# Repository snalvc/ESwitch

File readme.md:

# ESwitch

This is a high-side N-channel MOSFET electrical switch module. The power MOSFET (DMTH8003SPS) is driven by a high-side protection controller (LM5060). The schematics and PCB layout are designed in KiCad and available in the kicad directory. All the components are available in LCSC at least at the time of writing. It is also designed for single-sided PCBA with a few exceptions in the high current traces because you'll want them to be reinforced. Plus, I doubt XT90 can be assembled by cheap PCBAs anyway. There are also some Python utilities which are helpful for you to determine the required component values for various protections provided by the LM5060. In short:

- Calculate the required component values for the LM5060 with the help of programs in `utils`.
- Modify and generate the necessary manufacturing files in `kicad`.
- Have the PCB manufactured and assembled if you desire.
- Assemble the module with the instructions in `assemble`. You can also find the BOM there.

## TODO
- [ ] Fix XT90 socket and plug polarity
- [x] Add LCSC part numbers into schematics
- [ ] Add assemble instructions
- [ ] Add test results

## Debug Notes

I should have positioned the high-current traces on the bottom layer, allowing for reinforcement by adding solder or copper plates onto them.

Fortunately, by chance, I made a mistake with the XT90 socket and plug. Consequently, I can easily swap the socket and plug, relocating them to the back side of the board, thereby preventing any interference with the high-current traces.

## Assembled Module

Not the prettiest welding nor photography, but it works. You get the idea of the bugs that canceled each other out. The XT90s were meant to be on the top side, but the polarity (socket and plug) was wrong. In order to get the polarity (socket, plug) right, the XT90s need to be positioned on the bottom side when swapped, which luckily achieved the desired outcome (leaving top traces for reinforcement).

## Notes

2024-03-13: I have a module that has become consistently conductive. Electrostatic discharge (ESD) is suspected as the cause, especially considering it was originally functioning properly.

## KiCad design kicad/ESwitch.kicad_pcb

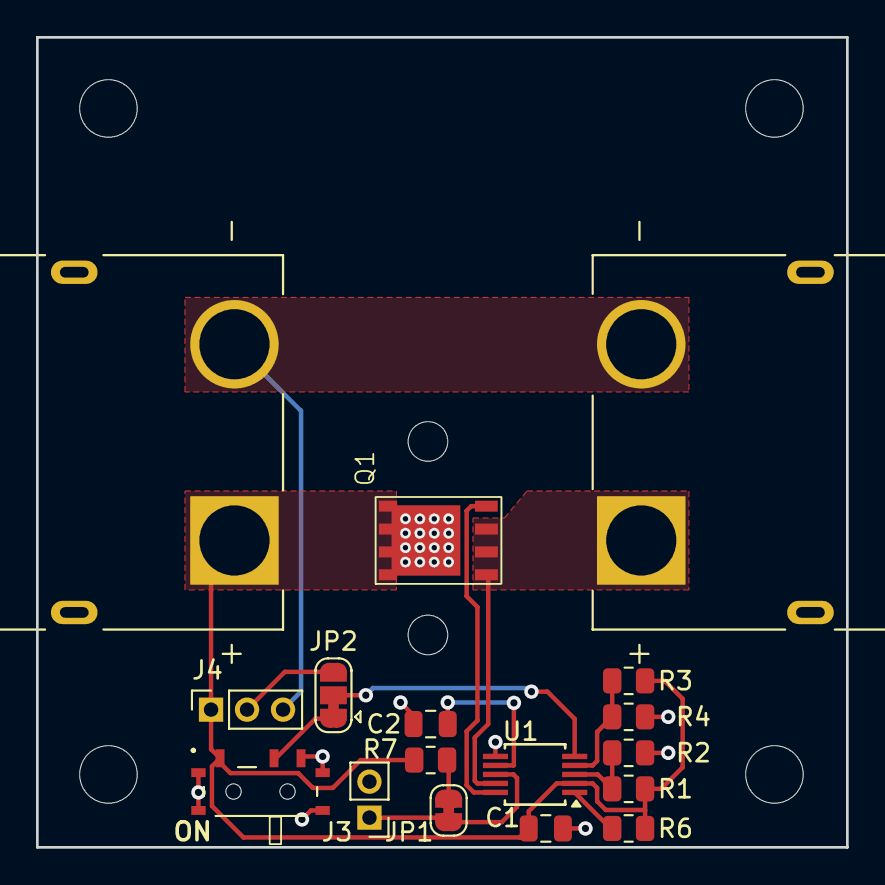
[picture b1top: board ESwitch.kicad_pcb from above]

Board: 2 copper layers, 45.0 x 45.0 mm, 17 parts (0 on the bottom side), 13 nets.

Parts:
C1: 0.1u; C_0805_2012Metric
C2: 68nF; C_0805_2012Metric
J1: XT90PW-F; AMASS_XT90PW-F
J2: XT90PW-M; AMASS_XT90PW-M
J3: Conn_01x02_Pin; PinHeader_1x02_P2.00mm_Vertical
J4: Conn_01x03_Socket; PinSocket_1x03_P2.00mm_Vertical
JP1: SolderJumper_2_Bridged; SolderJumper-2_P1.3mm_Bridged_RoundedPad1.0x1.5mm
JP2: Jumper_3_Bridged12; SolderJumper-3_P1.3mm_Bridged12_RoundedPad1.0x1.5mm
Q1: DMTH8003SPS-13; PowerDI5060-8 (Type K)
R1, R2, R3, R4: R; R_0805_2012Metric
R6: 75k; R_0805_2012Metric
R7: 10k; R_0805_2012Metric
SW1: MSK12C02
U1: LM5060; MSOP-10_3x3mm_P0.5mm

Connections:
+BATT: C1.1, J1.P (POS), J4.1, Q1.5 (D), Q1.6 (D), Q1.7 (D), Q1.8 (D), R1.1, R3.1, R6.1, R7.1, SW1.1 (A), U1.2 (VIN)
GND: C1.2, C2.2, J1.N (NEG), J2.N (NEG), J3.2, J4.3, R2.2, R4.2, SW1.3 (C), SW1.4, U1.6 (GND)
unnamed: J2.P (POS), Q1.1 (S), Q1.2 (S), Q1.3 (S), U1.9 (OUT)
unnamed: J3.1, JP1.1 (A), U1.8 (~PGD)
unnamed: J4.2, JP2.3 (B)
unnamed: JP1.2 (B), R7.2
unnamed: JP2.1 (A), SW1.2 (B)
unnamed: JP2.2 (C), U1.5 (EN)
unnamed: Q1.4 (G), U1.10 (GATE)
unnamed: R1.2, R2.1, U1.3 (OVP)
unnamed: R6.2, U1.1 (SENSE)
unnamed: C2.1, U1.7 (TIMER)
unnamed: R3.2, R4.1, U1.4 (UVLO)

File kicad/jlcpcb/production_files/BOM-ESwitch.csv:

Comment,Designator,Footprint,LCSC
68nF,C2,C_0805_2012Metric,C107159
10k,R7,R_0805_2012Metric,C17414
R,R2,R_0805_2012Metric,C17621
R,"R1,R3",R_0805_2012Metric,C17629
R,R4,R_0805_2012Metric,C17756
LM5060,U1,MSOP-10_3x3mm_P0.5mm,C2676940
0.1u,C1,C_0805_2012Metric,C28233
XT90PW-M,J2,AMASS_XT90PW-M,C3040689
XT90PW-F,J1,AMASS_XT90PW-F,C3040690
MSK12C02,SW1,MSK12C02,C431540
DMTH8003SPS-13,Q1,PowerDI5060-8 (Type K),C434455
75k,R6,R_0805_2012Metric,C84375
Conn_01x02_Pin,J3,PinHeader_1x02_P2.00mm_Vertical,
Jumper_3_Bridged12,JP2,SolderJumper-3_P1.3mm_Bridged12_RoundedPad1.0x1.5mm,
SolderJumper_2_Bridged,JP1,SolderJumper-2_P1.3mm_Bridged_RoundedPad1.0x1.5mm,
Conn_01x03_Socket,J4,PinSocket_1x03_P2.00mm_Vertical,

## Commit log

2024-03-07 init commit
2024-03-11 Add LCSC part numbers
2024-03-11 Add description for first assemble
2024-03-14 Add notes on a destructive event
